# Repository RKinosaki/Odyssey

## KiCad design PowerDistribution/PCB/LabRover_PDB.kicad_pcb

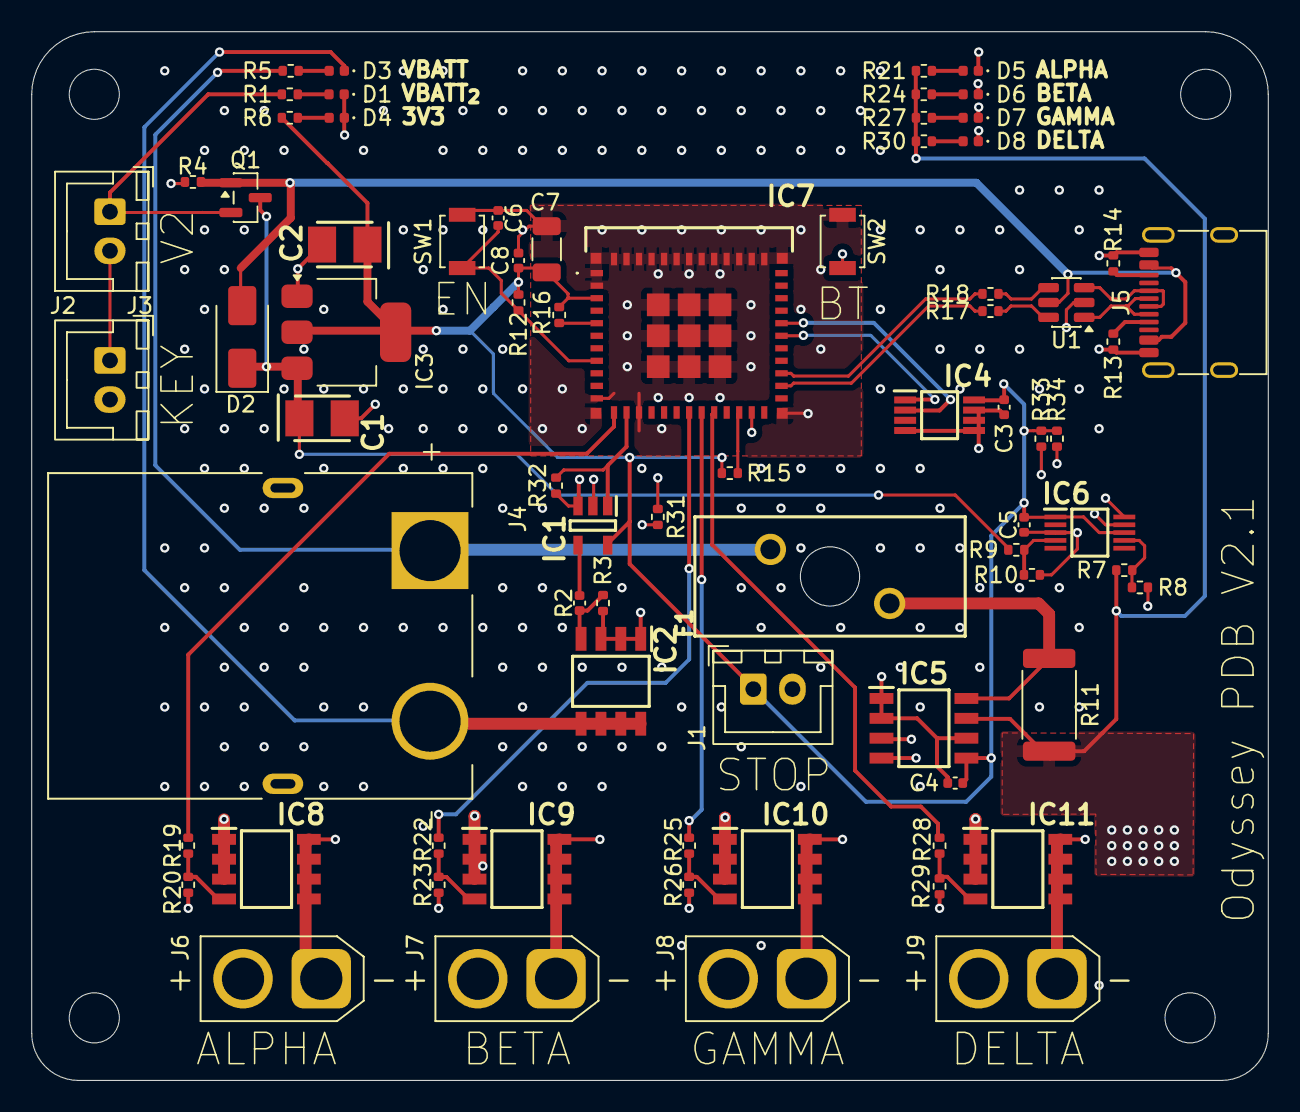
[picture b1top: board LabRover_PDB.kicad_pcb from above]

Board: 4 copper layers, 79.0 x 67.0 mm, 75 parts (0 on the bottom side), 49 nets.

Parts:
C1, C2: TAJB226K020RNJ
C3, C4, C8: 100n; C_0402_1005Metric
C5, C6: 1u; C_0402_1005Metric
C7: 22u; C_1206_3216Metric
D1, D3, D4: GREEN; LED_0402_1005Metric
D2: SS12; D_SMA
D5, D6, D7, D8: BLUE; LED_0402_1005Metric
F1: 01530008Z; 01530008
IC1: SN74LVC1G08DBVR
IC2, IC8, IC9, IC10, IC11: SI4162DY-T1-GE3
IC3: TLV1117LV33DCYR; SOT-223-3_TabPin2
IC4: LM75BDP,118
IC5: INA219AIDR
IC6: ADS1015BQDGSRQ1
IC7: ESP32-C3-MINI-1U-N4X; ESP32C3MINI1UN4X
J1, J2, J3: Conn_01x02; JST_XH_B2B-XH-A_1x02_P2.50mm_Vertical
J4: Conn_01x02; AMASS_XT90PW-M
J5: USB_C_Receptacle_USB2.0_16P; USB_C_Receptacle_G-Switch_GT-USB-7010ASV
J6, J7, J8, J9: Conn_01x02; XT30
Q1: BSS84; SOT-23
R1: 1kR; R_0402_1005Metric
R2: 100; C_0402_1005Metric
R3, R10, R12, R15, R16, R20, R23, R26, R29, R31, R32, R33, R34: 10k; R_0402_1005Metric
R4: 10kR; R_0402_1005Metric
R5: 2.4k; R_0402_1005Metric
R6: 600; R_0402_1005Metric
R7: 560k; R_0402_1005Metric
R8: 100k; R_0402_1005Metric
R9: 5.1k; R_0402_1005Metric
R11: 0.01; R_2512_6332Metric
R13, R14: 5K1; R_0402_1005Metric
R17, R18: 22; R_0402_1005Metric
R19, R22, R25, R28: 100; R_0402_1005Metric
R21, R24, R27, R30: 470; R_0402_1005Metric
SW1, SW2: SW_Push; SW_SPST_B3U-1000P
U1: USBLC6-2SC6; SOT-23-6

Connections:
+3.3V: C2.1 (+), C3.1, C4.1, C5.1, C7.1, C8.1, IC1.5 (VCC), IC3.2 (OUTPUT_1), IC4.8 (VCC), IC5.5 (VS), IC6.1 (ADDR), IC6.8 (VDD), IC7.3 (3V3), J1.1, R6.2, R12.2, R15.1, R16.1, R33.1, R34.1
+BATT_SENSED: IC5.7 (IN-), J6.2, J7.2, J8.2, J9.2, R7.1, R11.2, R21.2, R24.2, R27.2, R30.2
+VBATT_{2}: J3.1, Q1.2 (S), R1.2
/ESP32_C3/5V: D2.2 (A), J5.A4 (VBUS), J5.A9 (VBUS), J5.B4 (VBUS), J5.B9 (VBUS), Q1.1 (G), R4.2, U1.5 (VBUS)
/ESP32_C3/BOOT: IC7.23 (IO9), SW2.1
/ESP32_C3/D+: R18.2, U1.4 (I/O2)
/ESP32_C3/D-: R17.2, U1.6 (I/O1)
/ESP32_C3/DR+: IC7.27 (IO19), R18.1
/ESP32_C3/DR-: IC7.26 (IO18), R17.1
/ESP32_C3/GPIO0: IC7.12 (IO0), R19.2
/ESP32_C3/GPIO1: IC1.1 (A), IC7.13 (IO1), R32.2
/ESP32_C3/GPIO2: IC7.5 (IO2), R16.2
/ESP32_C3/GPIO4: IC7.18 (IO4), R22.2
/ESP32_C3/GPIO5: IC7.19 (IO5), R25.2
/ESP32_C3/GPIO6: IC7.20 (IO6), R28.2
/ESP32_C3/GPIO8: IC7.22 (IO8), R15.2
/ESP32_C3/GPIO20: IC4.1 (SDA), IC5.3 (SDA), IC6.9 (SDA), IC7.30 (RXD0), R33.2
/ESP32_C3/GPIO21: IC4.2 (SCL), IC5.4 (SCL), IC6.10 (SCL), IC7.31 (TXD0), R34.2
/ESP32_C3/RST: C6.1, IC7.8 (EN), R12.1, SW1.1
/ESP32_C3/USB_D+: J5.A6 (D+), J5.B6 (D+), U1.3 (I/O2)
/ESP32_C3/USB_D-: J5.A7 (D-), J5.B7 (D-), U1.1 (I/O1)
/Power_Protection/VBATT_{2}Read: C1.1 (+), D2.1 (K), IC3.3 (INPUT), Q1.3 (D), R9.1
/Sensors/AIN0: IC6.4 (AIN0), R9.2, R10.1
/Sensors/AIN3: IC6.7 (AIN3), R7.2, R8.1
/Sensors/IN+: F1.2, IC5.8 (IN+), R11.1
GND: C1.2 (-), C2.2 (-), C3.2, C4.2, C5.2, C6.2, C7.2, C8.2, D1.1 (K), D4.1 (K), IC1.3 (GND), IC2.1 (S_1), IC2.2 (S_2), IC2.3 (S_3), IC3.1 (GND), IC4.4 (GND), IC4.5 (A2), IC4.6 (A1), IC4.7 (A0), IC5.1 (A1), IC5.2 (A0), IC5.6 (GND), IC6.3 (GND), IC7.1 (GND_1), IC7.2 (GND_2), IC7.11 (GND_3), IC7.14 (GND_4), IC7.36 (GND_5), IC7.37 (GND_6), IC7.38 (GND_7), IC7.39 (GND_8), IC7.40 (GND_9), IC7.41 (GND_10), IC7.42 (GND_11), IC7.43 (GND_12), IC7.44 (GND_13), IC7.45 (GND_14), IC7.46 (GND_15), IC7.47 (GND_16), IC7.48 (GND_17), IC7.49 (GND_18), IC7.50 (GND_19), IC7.51 (GND_20), IC7.52 (GND_21), IC7.53 (GND_22), IC7.54 (GND_23), IC7.55 (GND_24), IC7.56 (GND_25), IC7.57 (GND_26), IC7.58 (GND_27), IC7.59 (GND_28), IC7.60 (GND_29), IC7.61 (GND_30), IC8.1 (S_1), IC8.2 (S_2), IC8.3 (S_3), IC9.1 (S_1), IC9.2 (S_2), IC9.3 (S_3), IC10.1 (S_1), IC10.2 (S_2), IC10.3 (S_3), IC11.1 (S_1), IC11.2 (S_2), IC11.3 (S_3), J2.2, J5.A1 (GND), J5.A12 (GND), J5.B1 (GND), J5.B12 (GND), R3.1, R4.1, R8.2, R10.2, R13.2, R14.1, R20.1, R23.1, R26.1, R29.1, R31.1, R32.1, SW1.2, SW2.2, U1.2 (GND)
unnamed: D1.2 (A), R1.1
unnamed: D3.2 (A), R5.1
unnamed: D3.1 (K), IC2.5 (D_1), IC2.6 (D_2), IC2.7 (D_3), IC2.8 (D_4)
unnamed: D4.2 (A), R6.1
unnamed: D5.2 (A), R21.1
unnamed: D5.1 (K), IC8.5 (D_1), IC8.6 (D_2), IC8.7 (D_3), IC8.8 (D_4), J6.1
unnamed: D6.2 (A), R24.1
unnamed: D6.1 (K), IC9.5 (D_1), IC9.6 (D_2), IC9.7 (D_3), IC9.8 (D_4), J7.1
unnamed: D7.2 (A), R27.1
unnamed: D7.1 (K), IC10.5 (D_1), IC10.6 (D_2), IC10.7 (D_3), IC10.8 (D_4), J8.1
unnamed: D8.2 (A), R30.1
unnamed: D8.1 (K), IC11.5 (D_1), IC11.6 (D_2), IC11.7 (D_3), IC11.8 (D_4), J9.1
unnamed: IC1.2 (B), J1.2, R31.2
unnamed: IC1.4 (Y), R2.1
unnamed: IC2.4 (G), R2.2, R3.2
unnamed: IC8.4 (G), R19.1, R20.2
unnamed: IC9.4 (G), R22.1, R23.2
unnamed: IC10.4 (G), R25.1, R26.2
unnamed: IC11.4 (G), R28.1, R29.2
unnamed: J2.1, J3.2
unnamed: F1.1, R5.2
unnamed: J5.A5 (CC1), R13.1
unnamed: J5.B5 (CC2), R14.2

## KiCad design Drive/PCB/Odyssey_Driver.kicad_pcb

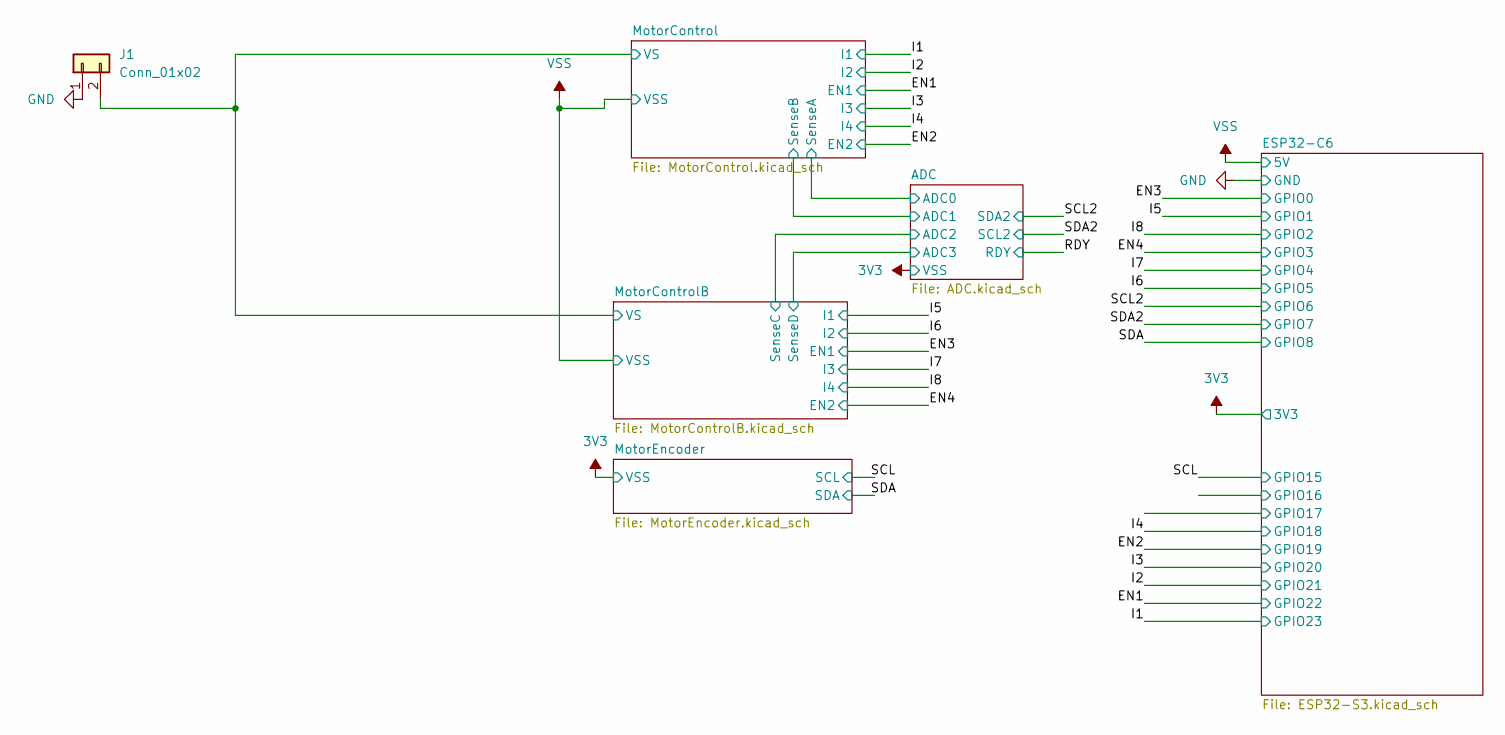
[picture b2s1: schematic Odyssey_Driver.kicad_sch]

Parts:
J1: Conn_01x02; AMASS_XT30PW-M_1x02_P2.50mm_Horizontal

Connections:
/MotorControl/VS: J1.2; also elsewhere on the board
GND: J1.1; also elsewhere on the board

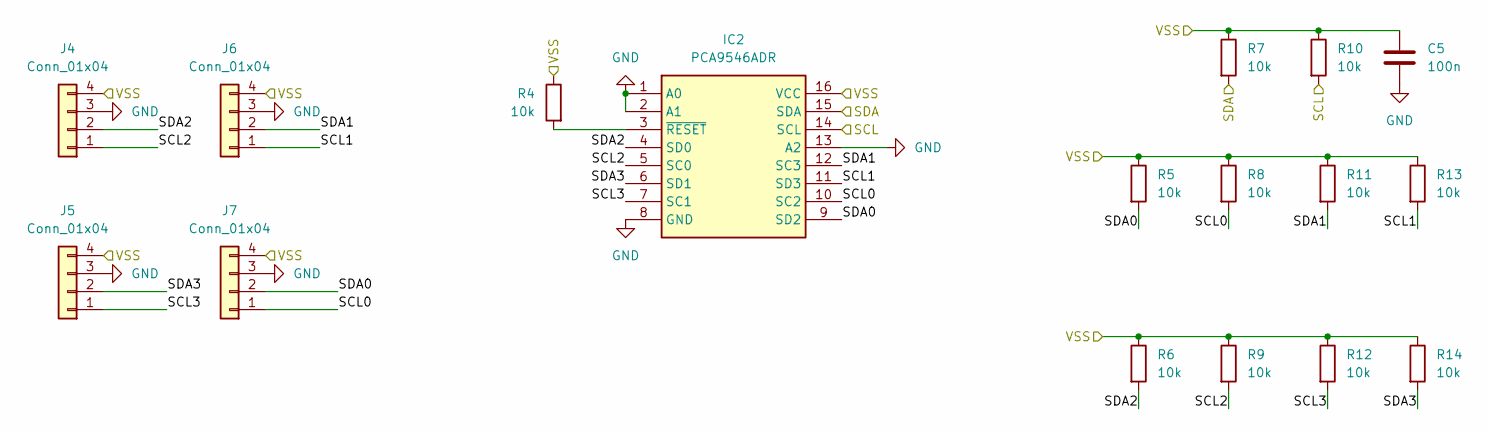
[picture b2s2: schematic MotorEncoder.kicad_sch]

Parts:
C5: 100n; C_0402_1005Metric
IC2: PCA9546ADR; SOIC127P600X175-16N; Mouser Part Number 595-PCA9546ADR
J4, J5, J6, J7: Conn_01x04; S4BXHSM4TBLFSN
R4, R5, R6, R7, R8, R9, R10, R11, R12, R13, R14: 10k; R_0402_1005Metric

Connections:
3V3: C5.1, IC2.16 (VCC), J4.4, J5.4, J6.4, J7.4, R4.1, R5.1, R6.1, R7.1, R8.1, R9.1, R10.1, R11.1, R12.1, R13.1, R14.1; also elsewhere on the board
/MotorEncoder/SCL0: IC2.10 (SC2), J7.1, R8.2
/MotorEncoder/SCL1: IC2.11 (SD3), J6.1, R13.2
/MotorEncoder/SCL2: IC2.5 (SC0), J4.1, R9.2
/MotorEncoder/SCL3: IC2.7 (SC1), J5.1, R12.2
/MotorEncoder/SDA0: IC2.9 (SD2), J7.2, R5.2
/MotorEncoder/SDA1: IC2.12 (SC3), J6.2, R11.2
/MotorEncoder/SDA2: IC2.4 (SD0), J4.2, R6.2
/MotorEncoder/SDA3: IC2.6 (SD1), J5.2, R14.2
/SCL: IC2.14 (SCL), R10.2; also elsewhere on the board
/SDA: IC2.15 (SDA), R7.2; also elsewhere on the board
GND: C5.2, IC2.1 (A0), IC2.2 (A1), IC2.8 (GND), IC2.13 (A2), J4.3, J5.3, J6.3, J7.3; also elsewhere on the board
unnamed: IC2.3 (~RESET), R4.2

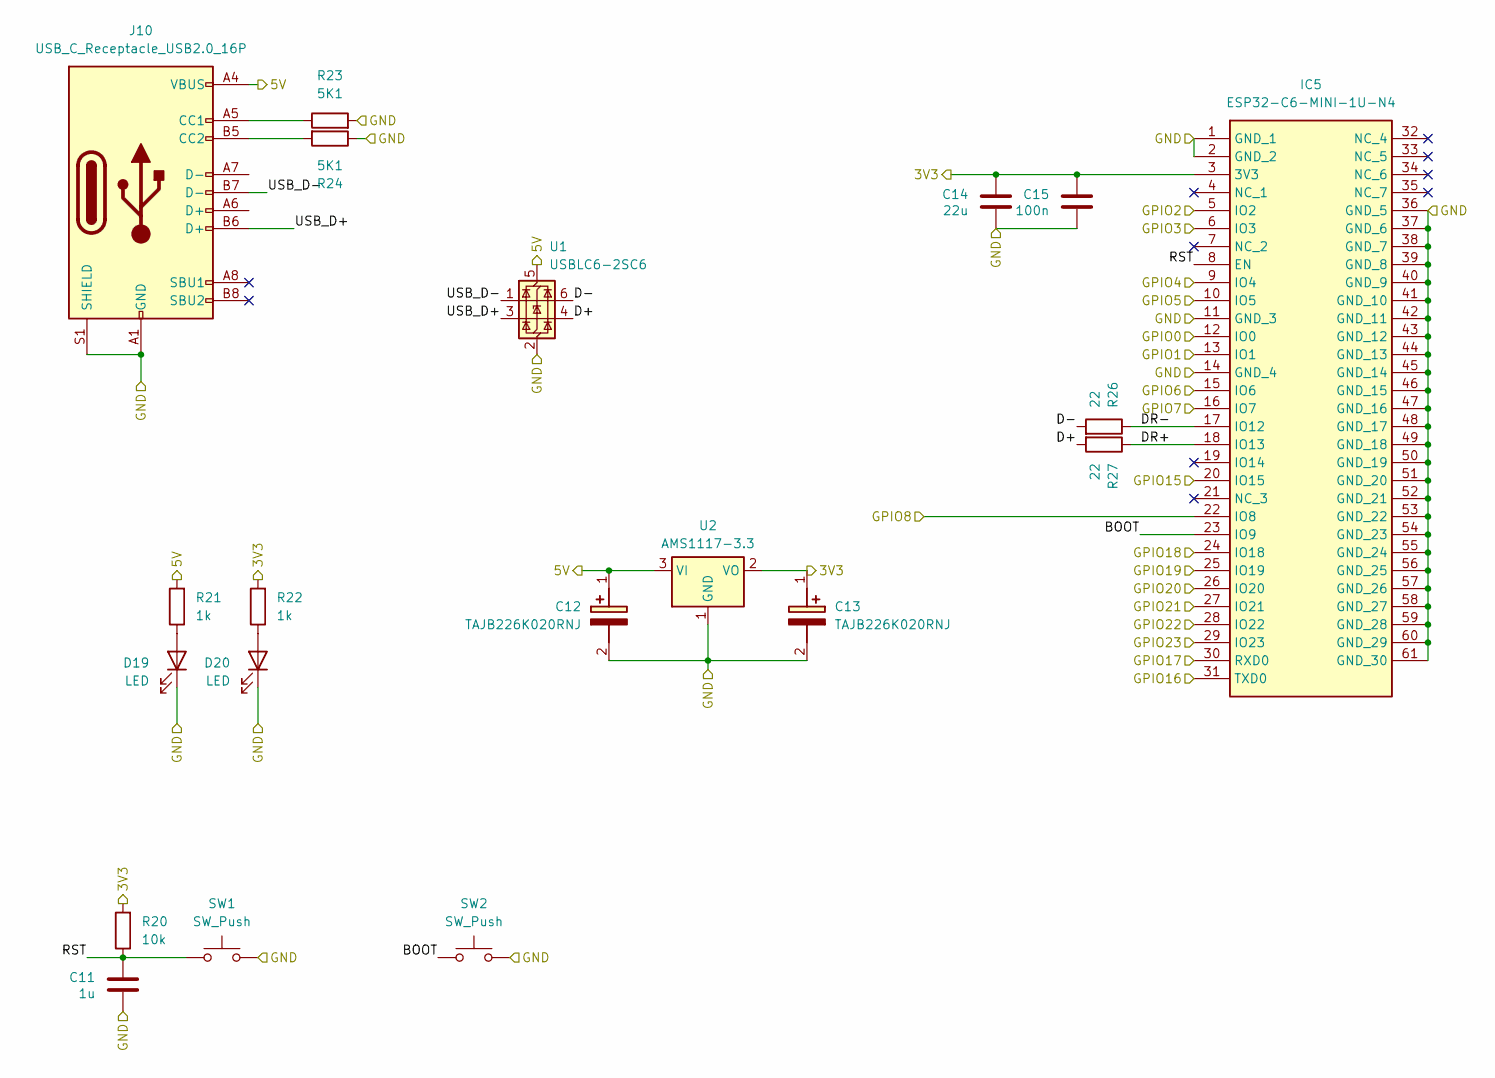
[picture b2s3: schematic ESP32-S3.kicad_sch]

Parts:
C11: 1u; C_0402_1005Metric
C12, C13: TAJB226K020RNJ; CAPPM3528X210N; Mouser Part Number 581-TAJB226K020R
C14: 22u; C_1206_3216Metric
C15: 100n; C_0402_1005Metric
D19, D20: LED; LED_0402_1005Metric
IC5: ESP32-C6-MINI-1U-N4; ESP32C6MINI1UN4; Mouser Part Number 356-ESP32-C6MINI1UN4
J10: USB_C_Receptacle_USB2.0_16P; USB_C_Receptacle_G-Switch_GT-USB-7010ASV
R20: 10k; R_0402_1005Metric
R21, R22: 1k; R_0402_1005Metric
R23, R24: 5K1; R_0402_1005Metric
R26, R27: 22; R_0402_1005Metric
SW1, SW2: SW_Push; SW_SPST_B3U-1000P
U1: USBLC6-2SC6; SOT-23-6
U2: AMS1117-3.3; SOT-223-3_TabPin2

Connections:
3V3: C13.1 (+), C14.1, C15.1, IC5.3 (3V3), R20.2, R22.2, U2.2 (VO); also elsewhere on the board
/EN1: IC5.28 (IO22); also elsewhere on the board
/EN2: IC5.25 (IO19); also elsewhere on the board
/EN3: IC5.12 (IO0); also elsewhere on the board
/EN4: IC5.6 (IO3); also elsewhere on the board
/ESP32-C6/BOOT: IC5.23 (IO9), SW2.1
/ESP32-C6/D+: R27.2, U1.4 (I/O2)
/ESP32-C6/D-: R26.2, U1.6 (I/O1)
/ESP32-C6/DR+: IC5.18 (IO13), R27.1
/ESP32-C6/DR-: IC5.17 (IO12), R26.1
/ESP32-C6/GPIO16: IC5.31 (TXD0)
/ESP32-C6/GPIO17: IC5.30 (RXD0)
/ESP32-C6/RST: C11.1, IC5.8 (EN), R20.1, SW1.1
/ESP32-C6/USB_D+: J10.B6 (D+), U1.3 (I/O2)
/ESP32-C6/USB_D-: J10.B7 (D-), U1.1 (I/O1)
/I1: IC5.29 (IO23); also elsewhere on the board
/I2: IC5.27 (IO21); also elsewhere on the board
/I3: IC5.26 (IO20); also elsewhere on the board
/I4: IC5.24 (IO18); also elsewhere on the board
/I5: IC5.13 (IO1); also elsewhere on the board
/I6: IC5.10 (IO5); also elsewhere on the board
/I7: IC5.9 (IO4); also elsewhere on the board
/I8: IC5.5 (IO2); also elsewhere on the board
/SCL: IC5.20 (IO15); also elsewhere on the board
/SCL2: IC5.15 (IO6); also elsewhere on the board
/SDA: IC5.22 (IO8); also elsewhere on the board
/SDA2: IC5.16 (IO7); also elsewhere on the board
GND: C11.2, C12.2 (-), C13.2 (-), C14.2, C15.2, D19.1 (K), D20.1 (K), IC5.1 (GND_1), IC5.2 (GND_2), IC5.11 (GND_3), IC5.14 (GND_4), IC5.36 (GND_5), IC5.37 (GND_6), IC5.38 (GND_7), IC5.39 (GND_8), IC5.40 (GND_9), IC5.41 (GND_10), IC5.42 (GND_11), IC5.43 (GND_12), IC5.44 (GND_13), IC5.45 (GND_14), IC5.46 (GND_15), IC5.47 (GND_16), IC5.48 (GND_17), IC5.49 (GND_18), IC5.50 (GND_19), IC5.51 (GND_20), IC5.52 (GND_21), IC5.53 (GND_22), IC5.54 (GND_23), IC5.55 (GND_24), IC5.56 (GND_25), IC5.57 (GND_26), IC5.58 (GND_27), IC5.59 (GND_28), IC5.60 (GND_29), IC5.61 (GND_30), J10.A1 (GND), J10.A12 (GND), J10.B1 (GND), J10.B12 (GND), J10.S1 (SHIELD), R23.2, R24.1, SW1.2, SW2.2, U1.2 (GND), U2.1 (GND); also elsewhere on the board
unnamed: D19.2 (A), R21.1
unnamed: D20.2 (A), R22.1
unnamed: J10.A5 (CC1), R23.1
unnamed: J10.B5 (CC2), R24.2
VSS: C12.1 (+), J10.A4 (VBUS), J10.A9 (VBUS), J10.B4 (VBUS), J10.B9 (VBUS), R21.2, U1.5 (VBUS), U2.3 (VI); also elsewhere on the board

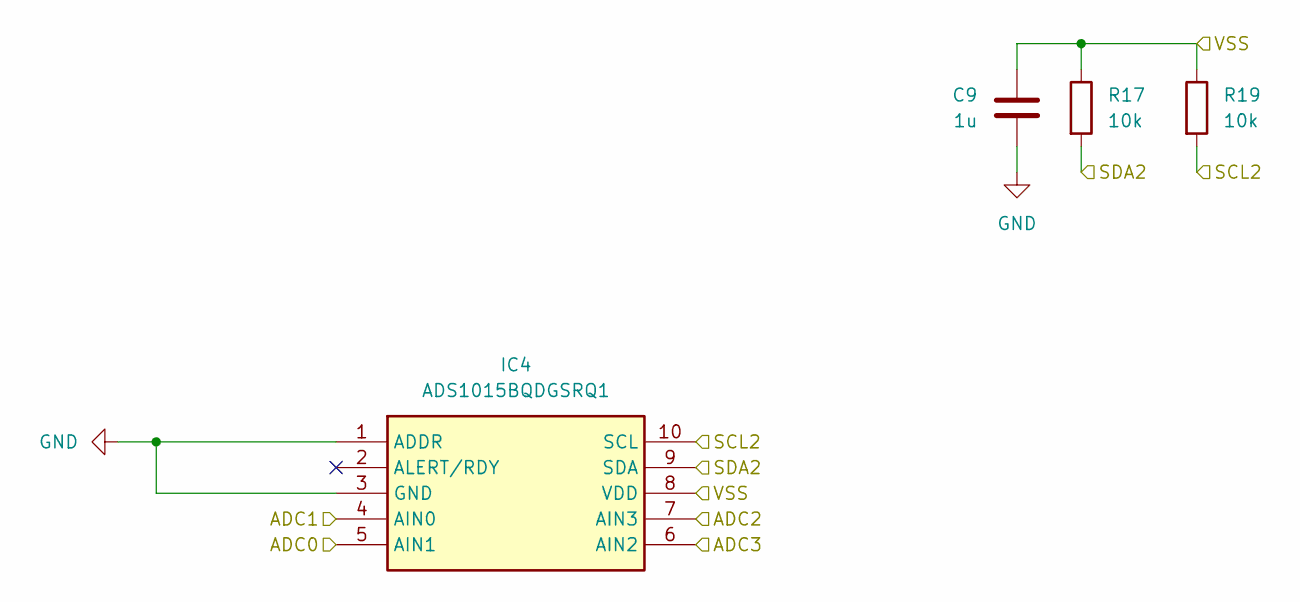
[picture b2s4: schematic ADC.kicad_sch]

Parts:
C9: 1u; C_0402_1005Metric
IC4: ADS1015BQDGSRQ1; SOP50P490X110-10N; Mouser Part Number 595-ADS1015BQDGSRQ1
R17, R19: 10k; R_0402_1005Metric

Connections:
3V3: C9.1, IC4.8 (VDD), R17.1, R19.1; also elsewhere on the board
/ADC/ADC0: IC4.5 (AIN1); also elsewhere on the board
/ADC/ADC1: IC4.4 (AIN0); also elsewhere on the board
/ADC/ADC2: IC4.7 (AIN3); also elsewhere on the board
/ADC/ADC3: IC4.6 (AIN2); also elsewhere on the board
/SCL2: IC4.9 (SDA), R17.2; also elsewhere on the board
/SDA2: IC4.10 (SCL), R19.2; also elsewhere on the board
GND: C9.2, IC4.1 (ADDR), IC4.3 (GND); also elsewhere on the board

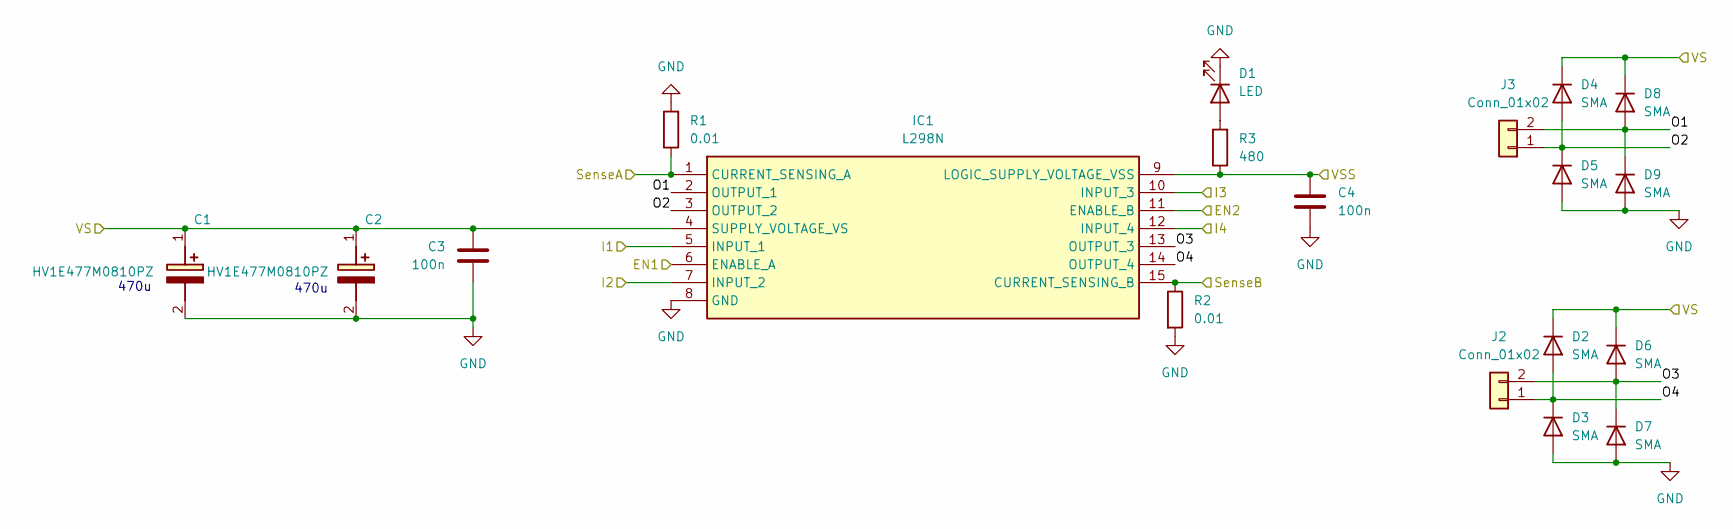
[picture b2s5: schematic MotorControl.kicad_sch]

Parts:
C1, C2: HV1E477M0810PZ; EEHZT1E331UP; Mouser Part Number 667-EEE-FT1E471GP
C3, C4: 100n; C_0402_1005Metric
D1: LED; LED_0402_1005Metric
D2, D3, D4, D5, D6, D7, D8, D9: SMA; D_SMA
IC1: L298N; TO127P500X2020X2210-15P; Mouser Part Number 511-L298
J2, J3: Conn_01x02; AMASS_XT30PW-F_1x02_P2.50mm_Horizontal
R1, R2: 0.01; R_2512_6332Metric
R3: 480; R_0402_1005Metric

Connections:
/ADC/ADC0: IC1.1 (CURRENT_SENSING_A), R1.1; also elsewhere on the board
/ADC/ADC1: IC1.15 (CURRENT_SENSING_B), R2.1; also elsewhere on the board
/EN1: IC1.6 (ENABLE_A); also elsewhere on the board
/EN2: IC1.11 (ENABLE_B); also elsewhere on the board
/I1: IC1.5 (INPUT_1); also elsewhere on the board
/I2: IC1.7 (INPUT_2); also elsewhere on the board
/I3: IC1.10 (INPUT_3); also elsewhere on the board
/I4: IC1.12 (INPUT_4); also elsewhere on the board
/MotorControl/O1: D8.2 (A), D9.1 (K), IC1.2 (OUTPUT_1), J3.2
/MotorControl/O2: D4.2 (A), D5.1 (K), IC1.3 (OUTPUT_2), J3.1
/MotorControl/O3: D6.2 (A), D7.1 (K), IC1.13 (OUTPUT_3), J2.2
/MotorControl/O4: D2.2 (A), D3.1 (K), IC1.14 (OUTPUT_4), J2.1
/MotorControl/VS: C1.1 (+), C2.1 (+), C3.1, D2.1 (K), D4.1 (K), D6.1 (K), D8.1 (K), IC1.4 (SUPPLY_VOLTAGE_VS); also elsewhere on the board
GND: C1.2 (-), C2.2 (-), C3.2, C4.2, D1.1 (K), D3.2 (A), D5.2 (A), D7.2 (A), D9.2 (A), IC1.8 (GND), R1.2, R2.2; also elsewhere on the board
unnamed: D1.2 (A), R3.2
VSS: C4.1, IC1.9 (LOGIC_SUPPLY_VOLTAGE_VSS), R3.1; also elsewhere on the board

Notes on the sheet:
470u

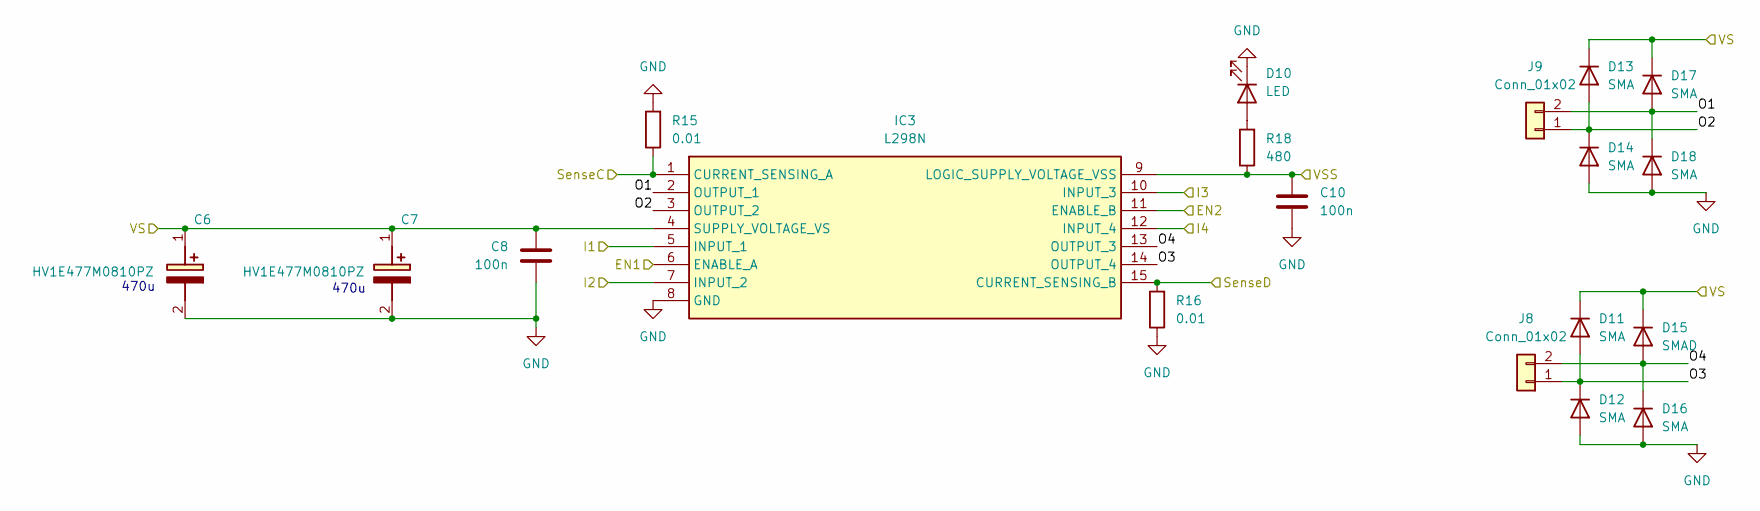
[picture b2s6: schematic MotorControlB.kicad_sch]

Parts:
C6, C7: HV1E477M0810PZ; EEHZT1E331UP; Mouser Part Number 667-EEE-FT1E471GP
C8, C10: 100n; C_0402_1005Metric
D10: LED; LED_0402_1005Metric
D11, D12, D13, D14, D16, D17, D18: SMA; D_SMA
D15: SMAD; D_SMA
IC3: L298N; TO127P500X2020X2210-15P; Mouser Part Number 511-L298
J8, J9: Conn_01x02; AMASS_XT30PW-F_1x02_P2.50mm_Horizontal
R15, R16: 0.01; R_2512_6332Metric
R18: 480; R_0402_1005Metric

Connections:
/ADC/ADC2: IC3.1 (CURRENT_SENSING_A), R15.1; also elsewhere on the board
/ADC/ADC3: IC3.15 (CURRENT_SENSING_B), R16.2; also elsewhere on the board
/EN3: IC3.6 (ENABLE_A); also elsewhere on the board
/EN4: IC3.11 (ENABLE_B); also elsewhere on the board
/I5: IC3.5 (INPUT_1); also elsewhere on the board
/I6: IC3.7 (INPUT_2); also elsewhere on the board
/I7: IC3.10 (INPUT_3); also elsewhere on the board
/I8: IC3.12 (INPUT_4); also elsewhere on the board
/MotorControl/VS: C6.1 (+), C7.1 (+), C8.1, D11.1 (K), D13.1 (K), D15.1 (K), D17.1 (K), IC3.4 (SUPPLY_VOLTAGE_VS); also elsewhere on the board
/MotorControlB/O1: D17.2 (A), D18.1 (K), IC3.2 (OUTPUT_1), J9.2
/MotorControlB/O2: D13.2 (A), D14.1 (K), IC3.3 (OUTPUT_2), J9.1
/MotorControlB/O3: D11.2 (A), D12.1 (K), IC3.14 (OUTPUT_4), J8.1
/MotorControlB/O4: D15.2 (A), D16.1 (K), IC3.13 (OUTPUT_3), J8.2
GND: C6.2 (-), C7.2 (-), C8.2, C10.2, D10.1 (K), D12.2 (A), D14.2 (A), D16.2 (A), D18.2 (A), IC3.8 (GND), R15.2, R16.1; also elsewhere on the board
unnamed: D10.2 (A), R18.2
VSS: C10.1, IC3.9 (LOGIC_SUPPLY_VOLTAGE_VSS), R18.1; also elsewhere on the board

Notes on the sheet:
470u

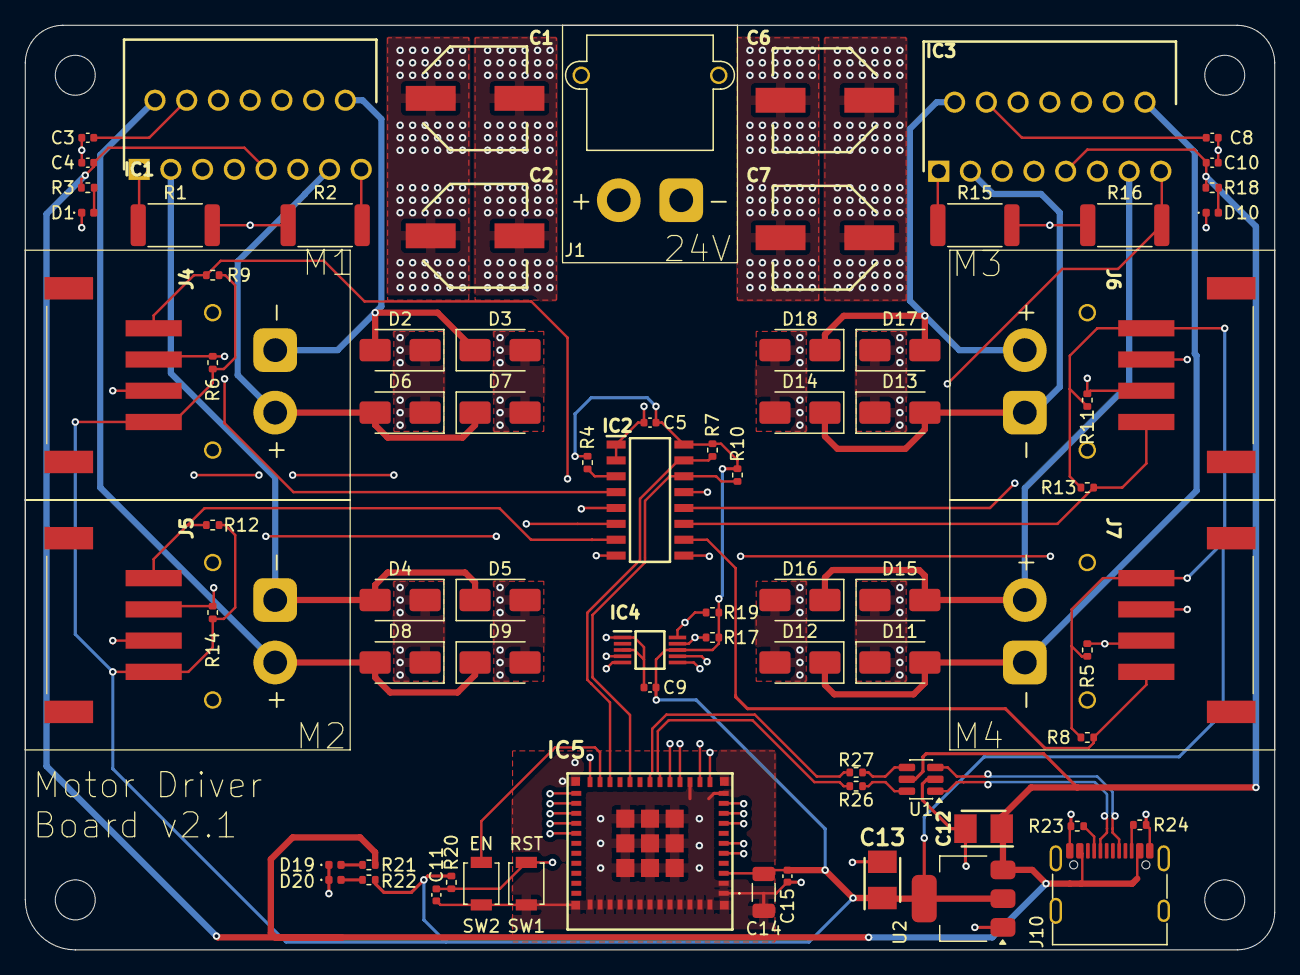
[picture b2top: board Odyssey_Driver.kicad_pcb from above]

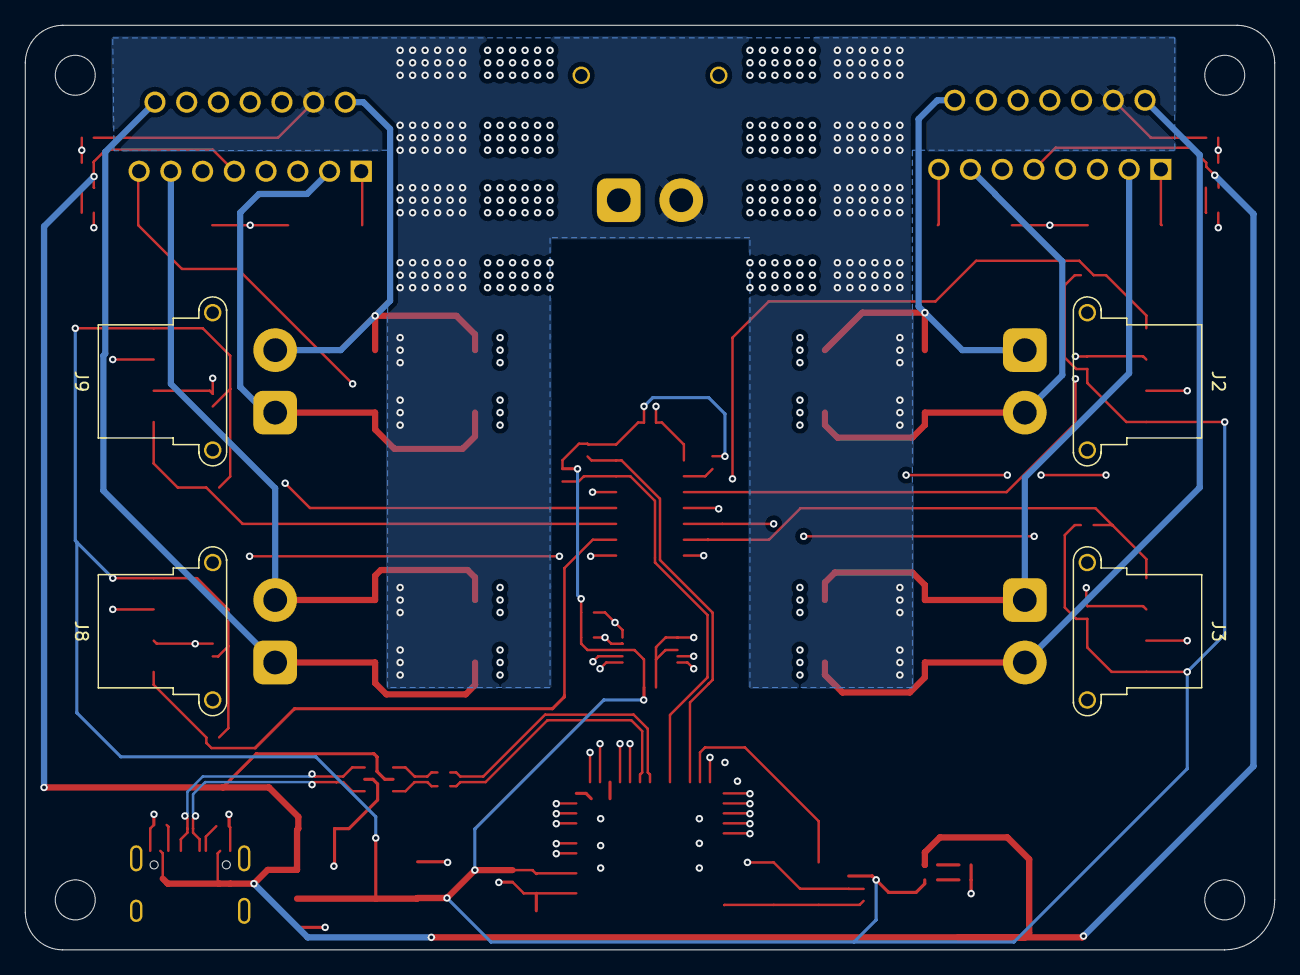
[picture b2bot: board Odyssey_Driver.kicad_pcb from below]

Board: 4 copper layers, 100.0 x 74.0 mm, 80 parts (4 on the bottom side), 55 nets.

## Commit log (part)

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2026-05-02 Adds V2.1 Driver Files
2026-05-03 Adds PDB v2.0
2026-05-25 Remapped to v2.1
